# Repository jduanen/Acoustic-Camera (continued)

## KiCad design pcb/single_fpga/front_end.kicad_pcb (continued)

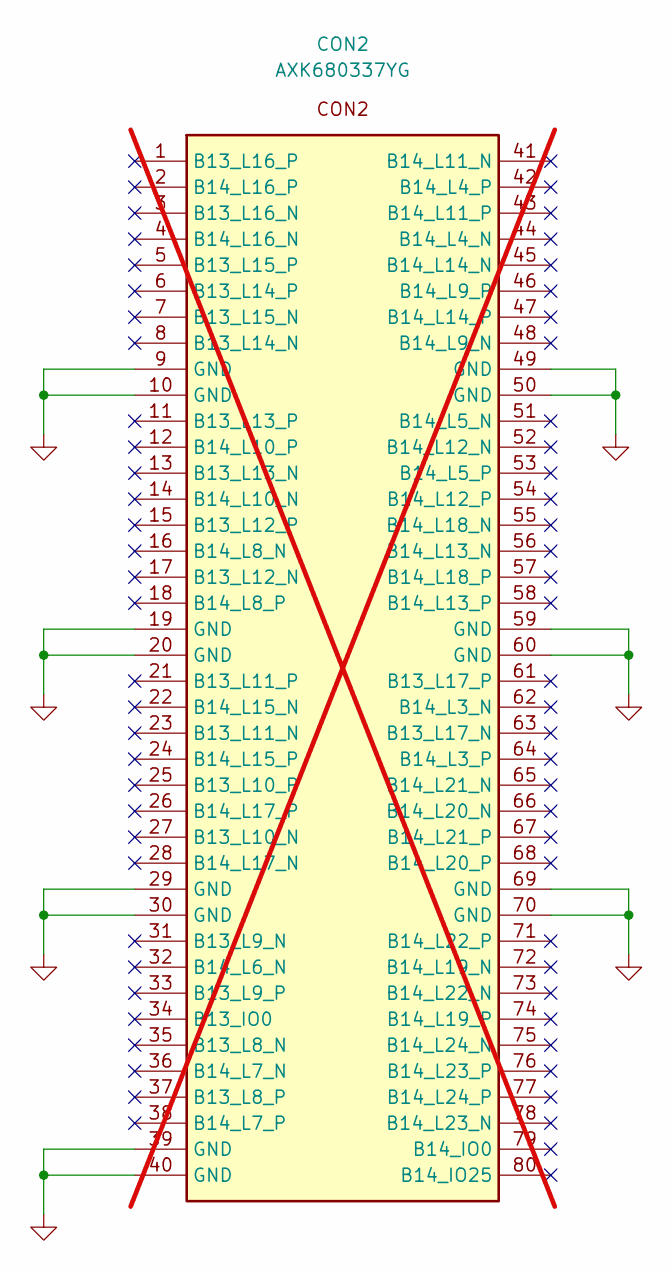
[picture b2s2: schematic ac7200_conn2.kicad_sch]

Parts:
CON2: AXK680337YG; Part Number AXK680337YG; LCSC Part # C2848859; not fitted

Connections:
GND: CON2.9 (GND), CON2.10 (GND), CON2.19 (GND), CON2.20 (GND), CON2.29 (GND), CON2.30 (GND), CON2.39 (GND), CON2.40 (GND), CON2.49 (GND), CON2.50 (GND), CON2.59 (GND), CON2.60 (GND), CON2.69 (GND), CON2.70 (GND); also elsewhere on the board

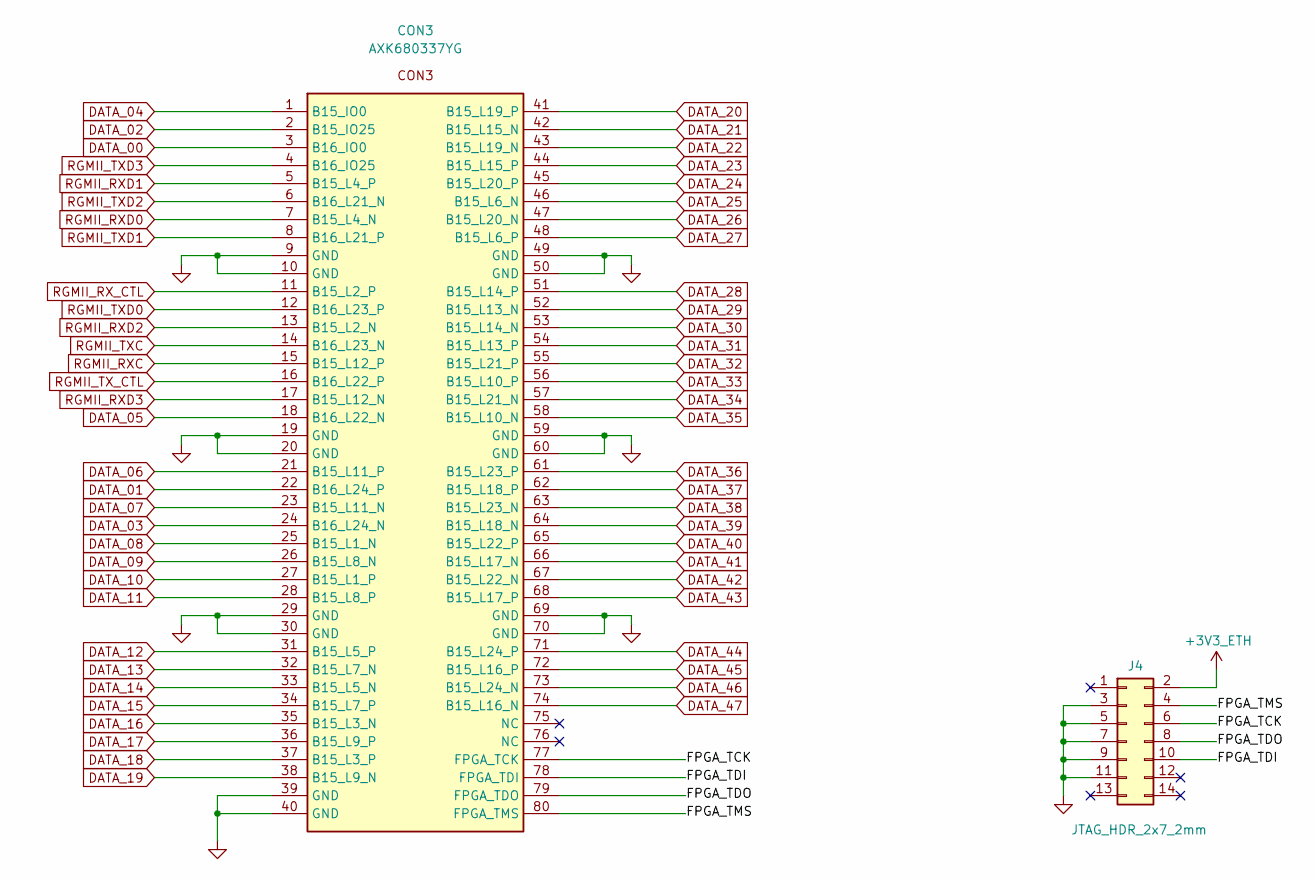
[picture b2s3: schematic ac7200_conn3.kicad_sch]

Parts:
CON3: AXK680337YG; Part Number AXK680337YG; LCSC Part # C2848859
J4: JTAG_HDR_2x7_2mm; PinHeader_2x07_P2.00mm_Vertical; Part Number PZ200-2-07-Z; LCSC Part # C2905993

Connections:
+3V3_ETH: J4.2; also elsewhere on the board
/AC7200 Conn3/FPGA_TCK: CON3.77 (FPGA_TCK), J4.6
/AC7200 Conn3/FPGA_TDI: CON3.78 (FPGA_TDI), J4.10
/AC7200 Conn3/FPGA_TDO: CON3.79 (FPGA_TDO), J4.8
/AC7200 Conn3/FPGA_TMS: CON3.80 (FPGA_TMS), J4.4
DATA_00: CON3.3 (B16_IO0); also elsewhere on the board
DATA_01: CON3.22 (B16_L24_P); also elsewhere on the board
DATA_02: CON3.2 (B15_IO25); also elsewhere on the board
DATA_03: CON3.24 (B16_L24_N); also elsewhere on the board
DATA_04: CON3.1 (B15_IO0); also elsewhere on the board
DATA_05: CON3.18 (B16_L22_N); also elsewhere on the board
DATA_06: CON3.21 (B15_L11_P); also elsewhere on the board
DATA_07: CON3.23 (B15_L11_N); also elsewhere on the board
DATA_08: CON3.25 (B15_L1_N); also elsewhere on the board
DATA_09: CON3.26 (B15_L8_N); also elsewhere on the board
DATA_10: CON3.27 (B15_L1_P); also elsewhere on the board
DATA_11: CON3.28 (B15_L8_P); also elsewhere on the board
DATA_12: CON3.31 (B15_L5_P); also elsewhere on the board
DATA_13: CON3.32 (B15_L7_N); also elsewhere on the board
DATA_14: CON3.33 (B15_L5_N); also elsewhere on the board
DATA_15: CON3.34 (B15_L7_P); also elsewhere on the board
DATA_16: CON3.35 (B15_L3_N); also elsewhere on the board
DATA_17: CON3.36 (B15_L9_P); also elsewhere on the board
DATA_18: CON3.37 (B15_L3_P); also elsewhere on the board
DATA_19: CON3.38 (B15_L9_N); also elsewhere on the board
DATA_20: CON3.41 (B15_L19_P); also elsewhere on the board
DATA_21: CON3.42 (B15_L15_N); also elsewhere on the board
DATA_22: CON3.43 (B15_L19_N); also elsewhere on the board
DATA_23: CON3.44 (B15_L15_P); also elsewhere on the board
DATA_24: CON3.45 (B15_L20_P); also elsewhere on the board
DATA_25: CON3.46 (B15_L6_N); also elsewhere on the board
DATA_26: CON3.47 (B15_L20_N); also elsewhere on the board
DATA_27: CON3.48 (B15_L6_P); also elsewhere on the board
DATA_28: CON3.51 (B15_L14_P); also elsewhere on the board
DATA_29: CON3.52 (B15_L13_N); also elsewhere on the board
DATA_30: CON3.53 (B15_L14_N); also elsewhere on the board
DATA_31: CON3.54 (B15_L13_P); also elsewhere on the board
DATA_32: CON3.55 (B15_L21_P); also elsewhere on the board
DATA_33: CON3.56 (B15_L10_P); also elsewhere on the board
DATA_34: CON3.57 (B15_L21_N); also elsewhere on the board
DATA_35: CON3.58 (B15_L10_N); also elsewhere on the board
DATA_36: CON3.61 (B15_L23_P); also elsewhere on the board
DATA_37: CON3.62 (B15_L18_P); also elsewhere on the board
DATA_38: CON3.63 (B15_L23_N); also elsewhere on the board
DATA_39: CON3.64 (B15_L18_N); also elsewhere on the board
DATA_40: CON3.65 (B15_L22_P); also elsewhere on the board
DATA_41: CON3.66 (B15_L17_N); also elsewhere on the board
DATA_42: CON3.67 (B15_L22_N); also elsewhere on the board
DATA_43: CON3.68 (B15_L17_P); also elsewhere on the board
DATA_44: CON3.71 (B15_L24_P); also elsewhere on the board
DATA_45: CON3.72 (B15_L16_P); also elsewhere on the board
DATA_46: CON3.73 (B15_L24_N); also elsewhere on the board
DATA_47: CON3.74 (B15_L16_N); also elsewhere on the board
GND: CON3.9 (GND), CON3.10 (GND), CON3.19 (GND), CON3.20 (GND), CON3.29 (GND), CON3.30 (GND), CON3.39 (GND), CON3.40 (GND), CON3.49 (GND), CON3.50 (GND), CON3.59 (GND), CON3.60 (GND), CON3.69 (GND), CON3.70 (GND), J4.3, J4.5, J4.7, J4.9, J4.11; also elsewhere on the board
RGMII_RXC: CON3.15 (B15_L12_P); also elsewhere on the board
RGMII_RXD0: CON3.7 (B15_L4_N); also elsewhere on the board
RGMII_RXD1: CON3.5 (B15_L4_P); also elsewhere on the board
RGMII_RXD2: CON3.13 (B15_L2_N); also elsewhere on the board
RGMII_RXD3: CON3.17 (B15_L12_N); also elsewhere on the board
RGMII_RX_CTL: CON3.11 (B15_L2_P); also elsewhere on the board
RGMII_TXC: CON3.14 (B16_L23_N); also elsewhere on the board
RGMII_TXD0: CON3.12 (B16_L23_P); also elsewhere on the board
RGMII_TXD1: CON3.8 (B16_L21_P); also elsewhere on the board
RGMII_TXD2: CON3.6 (B16_L21_N); also elsewhere on the board
RGMII_TXD3: CON3.4 (B16_IO25); also elsewhere on the board
RGMII_TX_CTL: CON3.16 (B16_L22_P); also elsewhere on the board

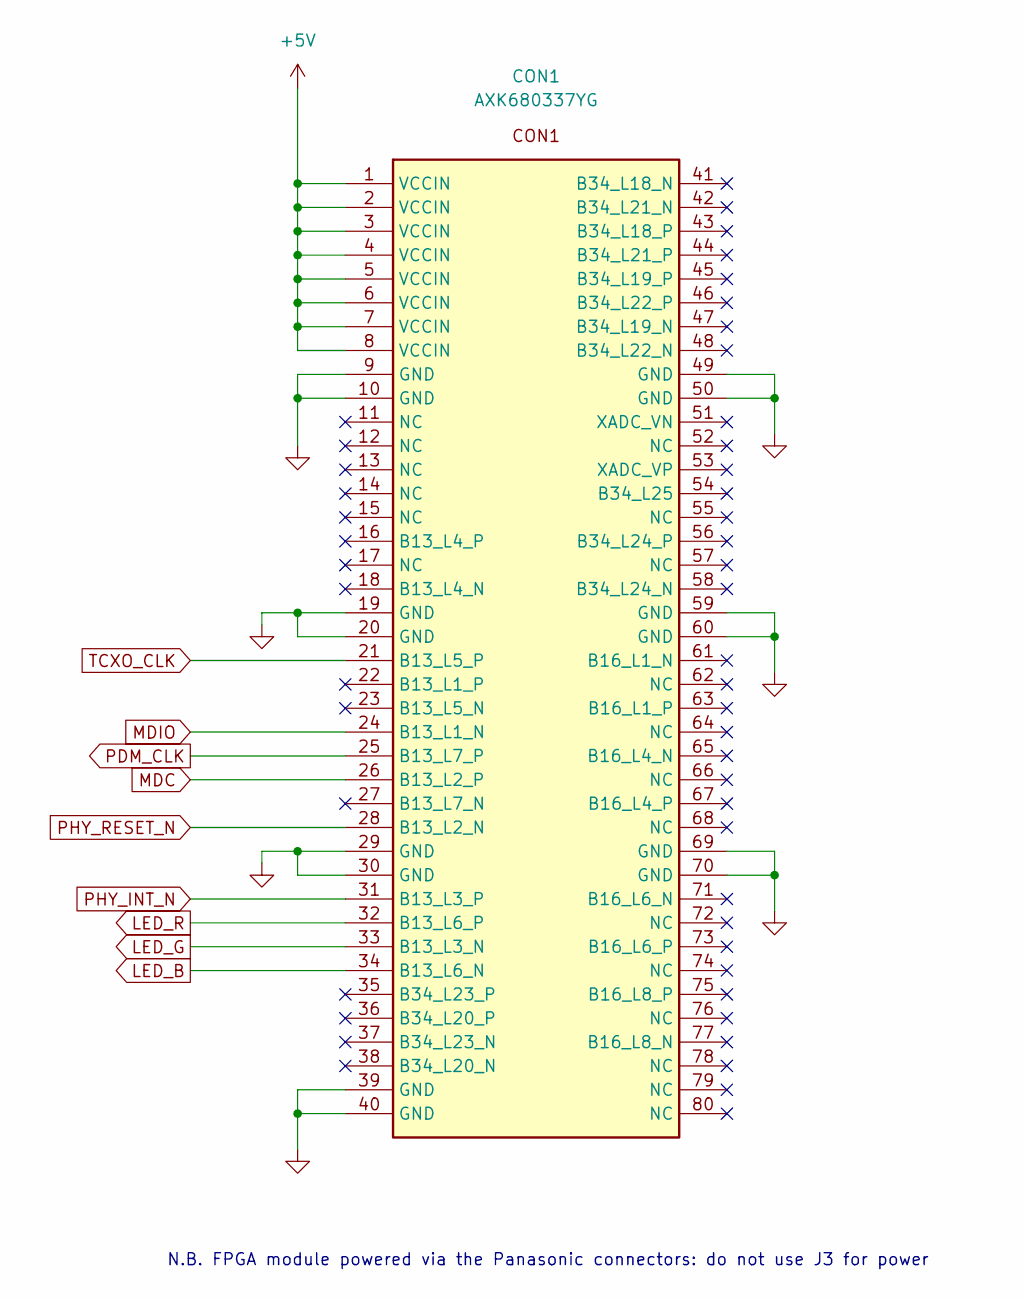
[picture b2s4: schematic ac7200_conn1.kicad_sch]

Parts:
CON1: AXK680337YG; Part Number AXK680337YG; LCSC Part # C2848859

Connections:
+5V: CON1.1 (VCCIN), CON1.2 (VCCIN), CON1.3 (VCCIN), CON1.4 (VCCIN), CON1.5 (VCCIN), CON1.6 (VCCIN), CON1.7 (VCCIN), CON1.8 (VCCIN); also elsewhere on the board
GND: CON1.9 (GND), CON1.10 (GND), CON1.19 (GND), CON1.20 (GND), CON1.29 (GND), CON1.30 (GND), CON1.39 (GND), CON1.40 (GND), CON1.49 (GND), CON1.50 (GND), CON1.59 (GND), CON1.60 (GND), CON1.69 (GND), CON1.70 (GND); also elsewhere on the board
LED_B: CON1.34 (B13_L6_N); also elsewhere on the board
LED_G: CON1.33 (B13_L3_N); also elsewhere on the board
LED_R: CON1.32 (B13_L6_P); also elsewhere on the board
MDC: CON1.26 (B13_L2_P); also elsewhere on the board
MDIO: CON1.24 (B13_L1_N); also elsewhere on the board
PDM_CLK: CON1.25 (B13_L7_P); also elsewhere on the board
PHY_INT_N: CON1.31 (B13_L3_P); also elsewhere on the board
PHY_RESET_N: CON1.28 (B13_L2_N); also elsewhere on the board
TCXO_CLK: CON1.21 (B13_L5_P); also elsewhere on the board

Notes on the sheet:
N.B. FPGA module powered via the Panasonic connectors: do not use J3 for power

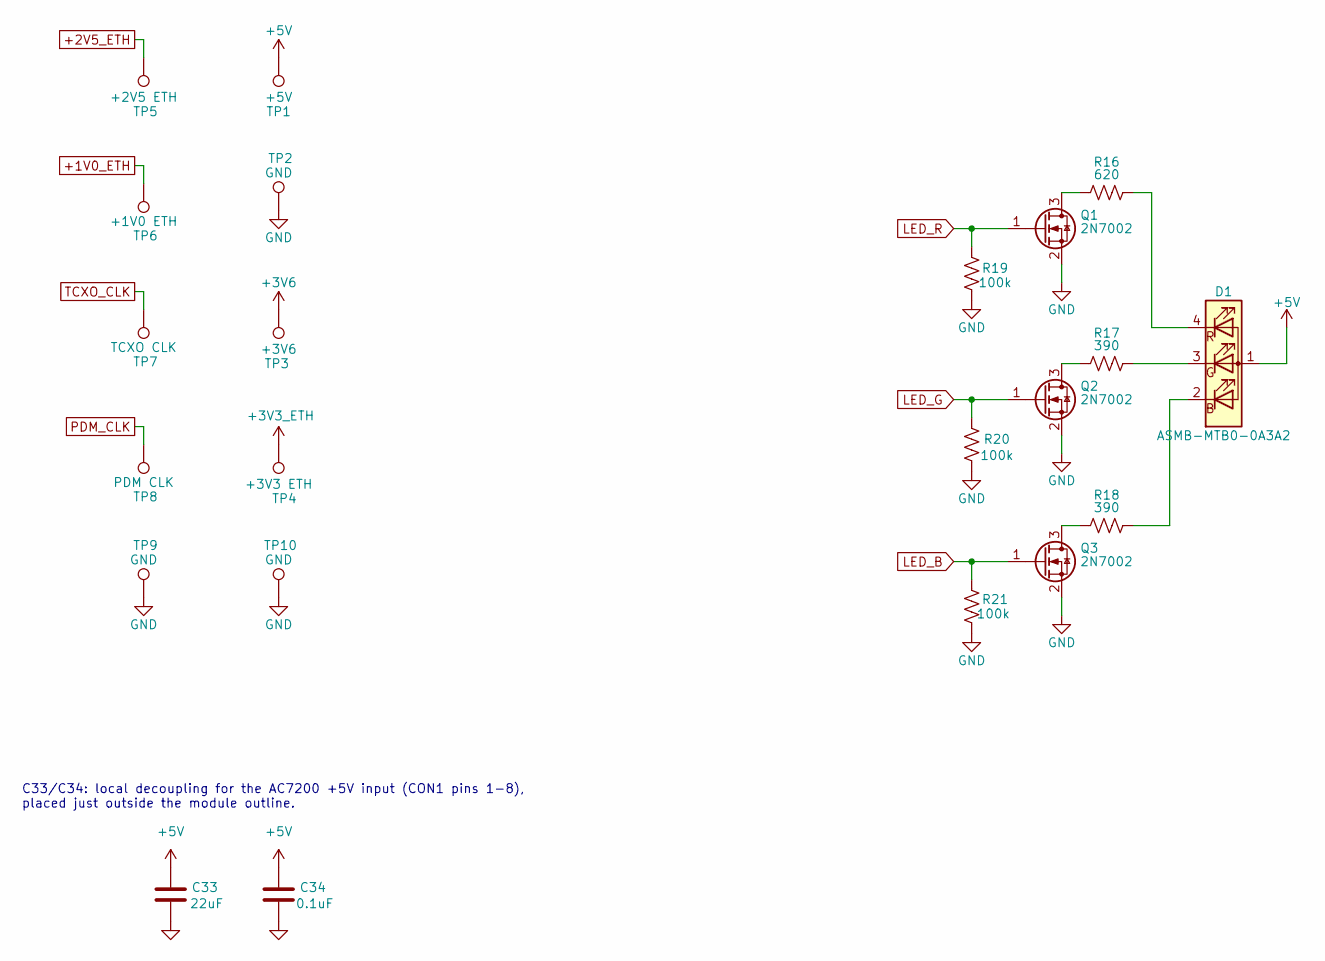
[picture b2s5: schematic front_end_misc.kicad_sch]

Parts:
C33: 22uF; C_0805_2012Metric; Part Number CL21A226MAQNNNE; LCSC Part # C45783
C34: 0.1uF; C_0402_1005Metric; Part Number CL05B104KO5NNNC; LCSC Part # C1525
D1: ASMB-MTB0-0A3A2; LED_Avago_PLCC4_3.2x2.8mm_CW; Part Number ASMB-MTB0-0A3A2; LCSC Part # C2686824
Q1, Q2, Q3: 2N7002; SOT-23; Part Number 2N7002; LCSC Part # C8545
R16: 620; R_0603_1608Metric; Part Number 0603WAF6200T5E; LCSC Part # C23220
R17, R18: 390; R_0603_1608Metric; Part Number 0603WAF3900T5E; LCSC Part # C23151
R19, R20, R21: 100k; R_0603_1608Metric; Part Number 0603WAF1003T5E; LCSC Part # C25803
TP1: +5V; TestPoint_THTPad_D2.0mm_Drill1.0mm
TP2, TP9, TP10: GND; TestPoint_THTPad_D2.0mm_Drill1.0mm
TP3: +3V6; TestPoint_THTPad_D2.0mm_Drill1.0mm
TP4: +3V3 ETH; TestPoint_THTPad_D2.0mm_Drill1.0mm
TP5: +2V5 ETH; TestPoint_THTPad_D2.0mm_Drill1.0mm
TP6: +1V0 ETH; TestPoint_THTPad_D2.0mm_Drill1.0mm
TP7: TCXO CLK; TestPoint_THTPad_D2.0mm_Drill1.0mm
TP8: PDM CLK; TestPoint_THTPad_D2.0mm_Drill1.0mm

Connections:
+1V0_ETH: TP6.1 (1_1); also elsewhere on the board
+2V5_ETH: TP5.1 (1_1); also elsewhere on the board
+3V3_ETH: TP4.1 (1_1); also elsewhere on the board
+3V6: TP3.1 (1_1); also elsewhere on the board
+5V: C33.1, C34.1, D1.1 (A), TP1.1 (1_1); also elsewhere on the board
GND: C33.2, C34.2, Q1.2 (S), Q2.2 (S), Q3.2 (S), R19.1, R20.1, R21.1, TP2.1 (1_1), TP9.1 (1_1), TP10.1 (1_1); also elsewhere on the board
LED_B: Q3.1 (G), R21.2; also elsewhere on the board
LED_G: Q2.1 (G), R20.2; also elsewhere on the board
LED_R: Q1.1 (G), R19.2; also elsewhere on the board
unnamed: D1.2 (BK), R18.1
unnamed: D1.3 (GK), R17.1
unnamed: D1.4 (RK), R16.1
unnamed: Q1.3 (D), R16.2
unnamed: Q2.3 (D), R17.2
unnamed: Q3.3 (D), R18.2
PDM_CLK: TP8.1 (1_1); also elsewhere on the board
TCXO_CLK: TP7.1 (1_1); also elsewhere on the board

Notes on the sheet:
C33/C34: local decoupling for the AC7200 +5V input (CON1 pins 1-8), placed just outside the module outline.

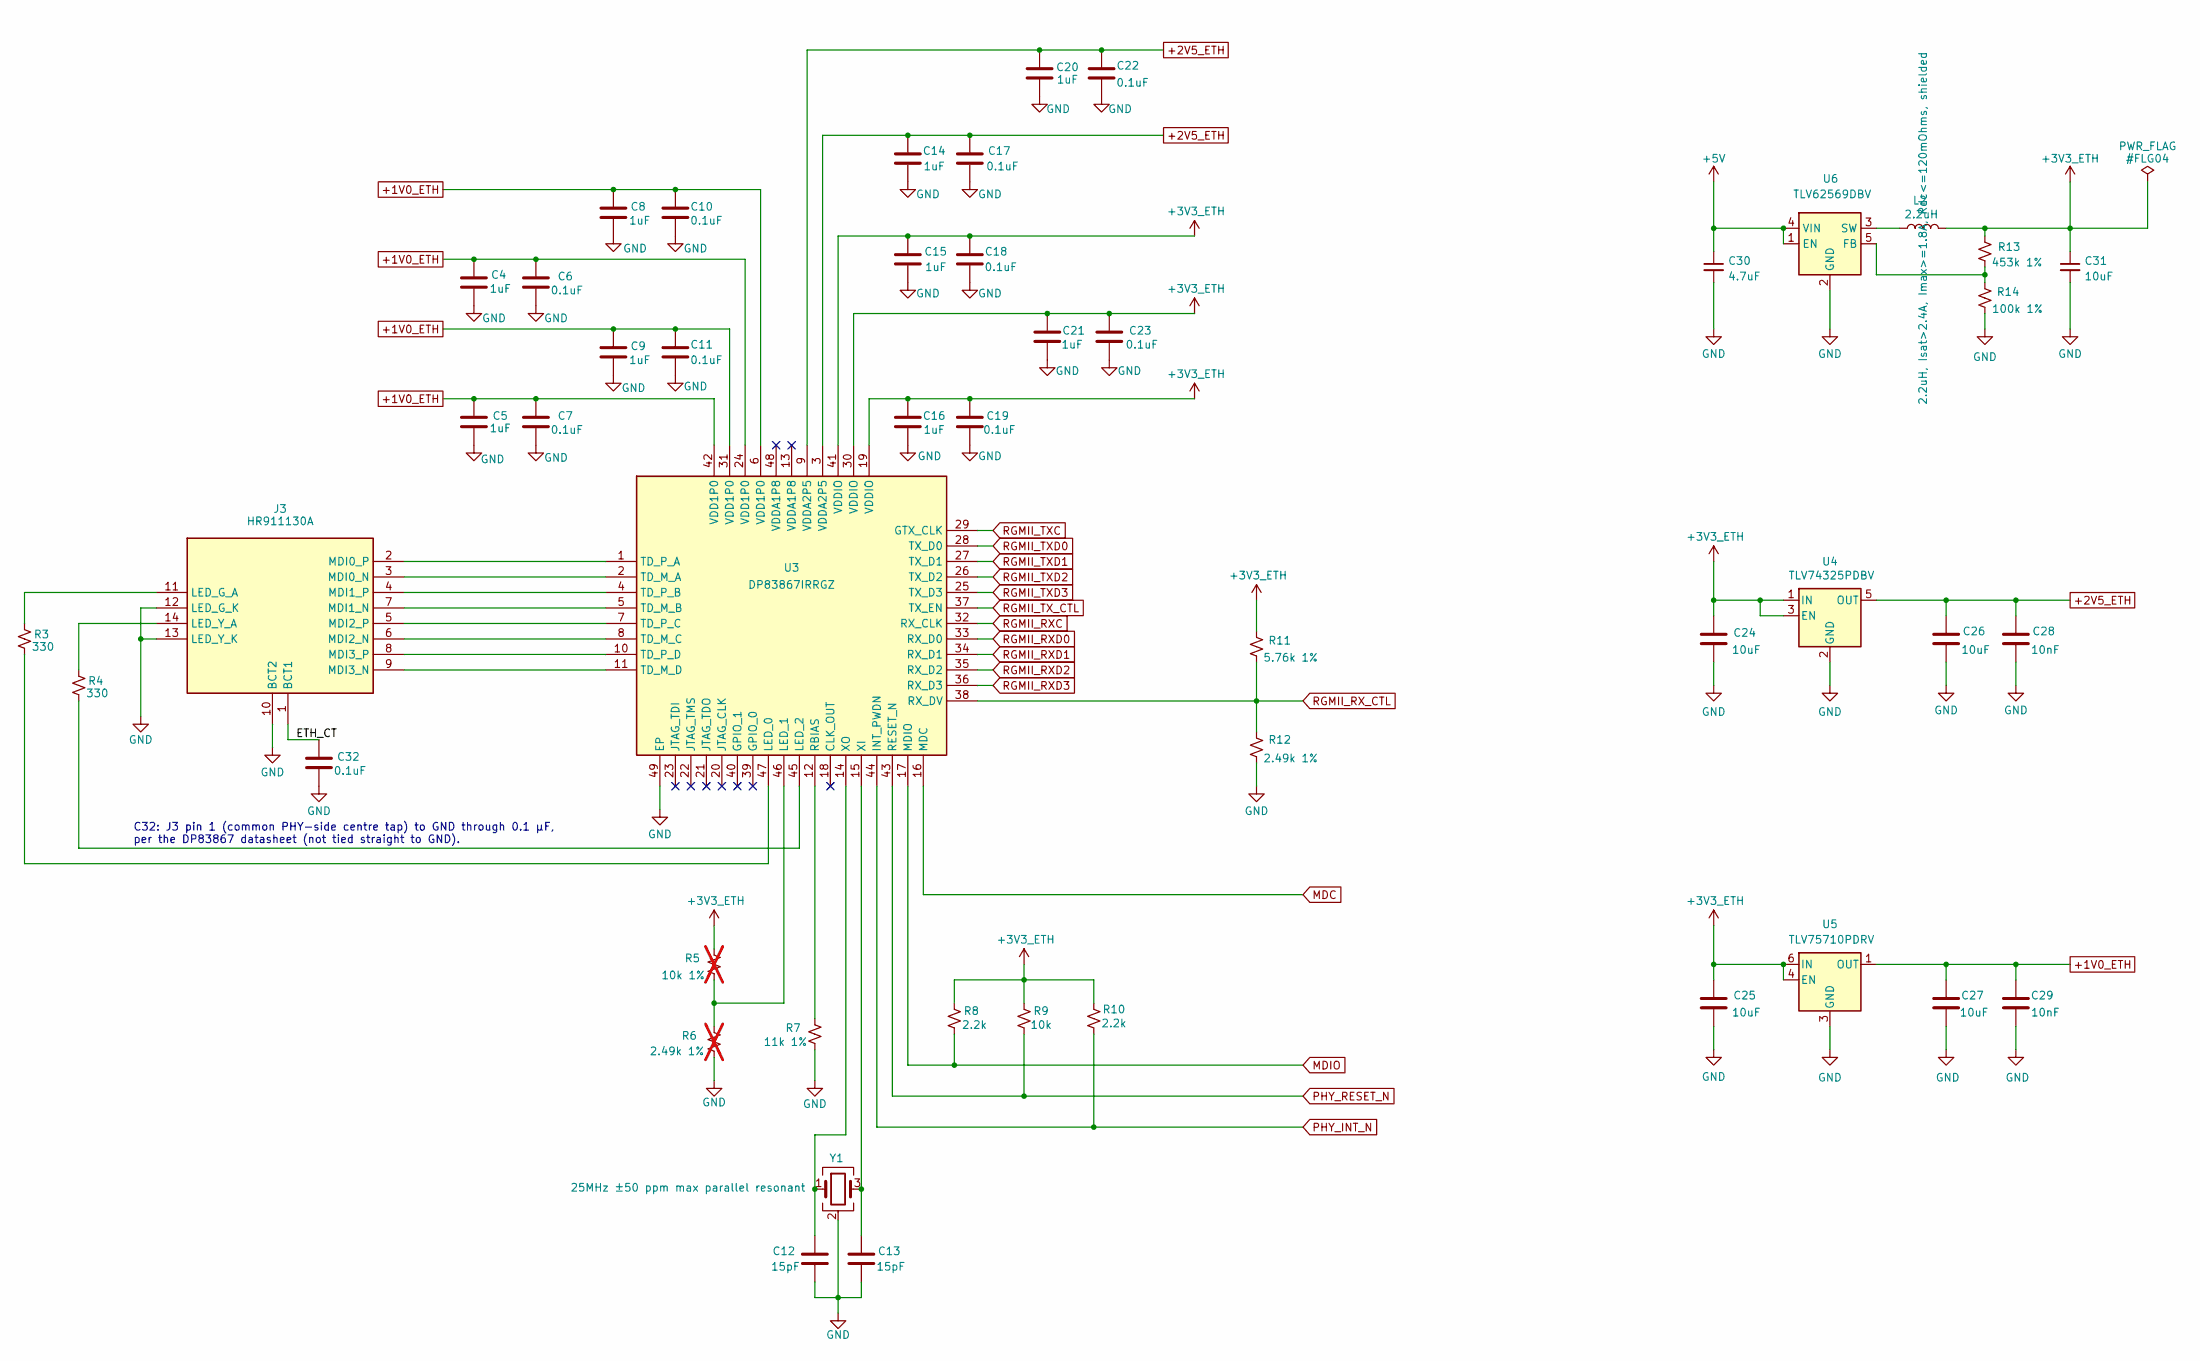
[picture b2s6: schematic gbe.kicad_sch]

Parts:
C4, C5, C8, C9, C14, C15, C16, C20, C21: 1uF; C_0402_1005Metric; Part Number CL05A105KA5NQNC; LCSC Part # C52923
C6, C7, C10, C11, C17, C18, C19, C22, C23, C32: 0.1uF; C_0402_1005Metric; Part Number CL05B104KO5NNNC; LCSC Part # C1525
C12, C13: 15pF; C_0402_1005Metric; Part Number 0402CG150J500NT; LCSC Part # C1548
C24, C25, C26, C27: 10uF; C_0603_1608Metric; Part Number CL10A106KP8NNNC; LCSC Part # C19702
C28, C29: 10nF; C_0603_1608Metric; Part Number 0603B103K500NT; LCSC Part # C57112
C30: 4.7uF; C_0805_2012Metric; Voltage 16V; Tolerance 10%; Part Number CL21B475KOFNNNE; LCSC Part # C107365
C31: 10uF; C_0805_2012Metric; Voltage 10V; Tolerance 10%; Part Number GRM21BR71A106KE51L; LCSC Part # C86038
J3: HR911130A; Part Number HR911130A; LCSC Part # C54408
L2: 2.2uH; L_Murata_DFE201610P; Part Number DFE201612E-2R2M=P2; LCSC Part # C337893
R3, R4: 330; R_0402_1005Metric; Part Number 0402WGF3300TCE; LCSC Part # C25104
R5: 10k 1%; R_0402_1005Metric; not fitted
R6: 2.49k 1%; R_0402_1005Metric; Part Number 0402WGF2491TCE; LCSC Part # C25884; not fitted
R7: 11k 1%; R_0402_1005Metric; Part Number 0402WGF1102TCE; LCSC Part # C25749
R8, R10: 2.2k; R_0402_1005Metric; Part Number 0402WGF2201TCE; LCSC Part # C25879
R9: 10k; R_0402_1005Metric; Part Number 0402WGF1002TCE; LCSC Part # C25744
R11: 5.76k 1%; R_0402_1005Metric; Part Number 0402WGF5761TCE; LCSC Part # C25910
R12: 2.49k 1%; R_0402_1005Metric; Part Number 0402WGF2491TCE; LCSC Part # C25884
R13: 453k 1%; R_0603_1608Metric; Tolerance 1%; Part Number ERJ-3EKF4533V; LCSC Part # C403234
R14: 100k 1%; R_0603_1608Metric; Tolerance 1%; Part Number 0603WAF1003T5E; LCSC Part # C25803
U3: DP83867IRRGZ; VQFN-48-1EP_7x7mm_P0.5mm_EP4.1x4.1mm; Part Number DP83867IRRGZR; LCSC Part # C2678038
U4: TLV74325PDBV; SOT-23-5; Part Number TLV74325PDBVR; LCSC Part # C485154
U5: TLV75710PDRV; WSON-6-1EP_2x2mm_P0.65mm_EP1x1.6mm; Part Number TLV75710PDRVR; LCSC Part # C2861391
U6: TLV62569DBV; SOT-23-5; Part Number TLV62569DBVR; LCSC Part # C141836
Y1: 25MHz ±50 ppm max parallel resonant; Crystal_SMD_3225-4Pin_3.2x2.5mm; Part Number X322525MOB4SI; LCSC Part # C9006

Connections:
+1V0_ETH: C4.1, C5.1, C6.1, C7.1, C8.1, C9.1, C10.1, C11.1, C27.2, C29.2, U3.6 (VDD1P0), U3.24 (VDD1P0), U3.31 (VDD1P0), U3.42 (VDD1P0), U5.1 (OUT); also elsewhere on the board
+2V5_ETH: C14.1, C17.1, C20.1, C22.1, C26.2, C28.2, U3.3 (VDDA2P5), U3.9 (VDDA2P5), U4.5 (OUT); also elsewhere on the board
+3V3_ETH: C15.1, C16.1, C18.1, C19.2, C21.1, C23.1, C24.2, C25.2, C31.1, L2.2, R5.2, R8.1, R9.1, R10.1, R11.2, R13.1, U3.19 (VDDIO), U3.30 (VDDIO), U3.41 (VDDIO), U4.1 (IN), U4.3 (EN), U5.4 (EN), U5.6 (IN); also elsewhere on the board
+5V: C30.1, U6.1 (EN), U6.4 (VIN); also elsewhere on the board
/Ethernet Interface/ETH_CT: C32.1, J3.1 (BCT1)
GND: C4.2, C5.2, C6.2, C7.2, C8.2, C9.2, C10.2, C11.2, C12.2, C13.2, C14.2, C15.2, C16.2, C17.2, C18.2, C19.1, C20.2, C21.2, C22.2, C23.2, C24.1, C25.1, C26.1, C27.1, C28.1, C29.1, C30.2, C31.2, C32.2, J3.10 (BCT2), J3.12 (LED_G_K), J3.13 (LED_Y_K), R6.1, R7.1, R12.1, R14.1, U3.49 (EP), U4.2 (GND), U5.3 (GND), U5.7 (GND), U6.2 (GND), Y1.2 (G), Y1.4 (G); also elsewhere on the board
MDC: U3.16 (MDC); also elsewhere on the board
MDIO: R8.2, U3.17 (MDIO); also elsewhere on the board
unnamed: J3.11 (LED_G_A), R3.1
unnamed: J3.14 (LED_Y_A), R4.2
unnamed: J3.3 (MDI0_N), U3.2 (TD_M_A)
unnamed: J3.2 (MDI0_P), U3.1 (TD_P_A)
unnamed: J3.7 (MDI1_N), U3.5 (TD_M_B)
unnamed: J3.4 (MDI1_P), U3.4 (TD_P_B)
unnamed: J3.6 (MDI2_N), U3.8 (TD_M_C)
unnamed: J3.5 (MDI2_P), U3.7 (TD_P_C)
unnamed: J3.9 (MDI3_N), U3.11 (TD_M_D)
unnamed: J3.8 (MDI3_P), U3.10 (TD_P_D)
unnamed: R3.2, U3.47 (LED_0)
unnamed: R5.1, R6.2, U3.46 (LED_1)
unnamed: R4.1, U3.45 (LED_2)
unnamed: R7.2, U3.12 (RBIAS)
unnamed: C13.1, U3.15 (XI), Y1.3
unnamed: C12.1, U3.14 (XO), Y1.1
unnamed: R13.2, R14.2, U6.5 (FB)
unnamed: L2.1, U6.3 (SW)
PHY_INT_N: R10.2, U3.44 (INT_PWDN); also elsewhere on the board
PHY_RESET_N: R9.2, U3.43 (RESET_N); also elsewhere on the board
RGMII_RXC: U3.32 (RX_CLK); also elsewhere on the board
RGMII_RXD0: U3.33 (RX_D0); also elsewhere on the board
RGMII_RXD1: U3.34 (RX_D1); also elsewhere on the board
RGMII_RXD2: U3.35 (RX_D2); also elsewhere on the board
RGMII_RXD3: U3.36 (RX_D3); also elsewhere on the board
RGMII_RX_CTL: R11.1, R12.2, U3.38 (RX_DV); also elsewhere on the board
RGMII_TXC: U3.29 (GTX_CLK); also elsewhere on the board
RGMII_TXD0: U3.28 (TX_D0); also elsewhere on the board
RGMII_TXD1: U3.27 (TX_D1); also elsewhere on the board
RGMII_TXD2: U3.26 (TX_D2); also elsewhere on the board
RGMII_TXD3: U3.25 (TX_D3); also elsewhere on the board
RGMII_TX_CTL: U3.37 (TX_EN); also elsewhere on the board

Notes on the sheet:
C32: J3 pin 1 (common PHY-side centre tap) to GND through 0.1 µF, per the DP83867 datasheet (not tied straight to GND).

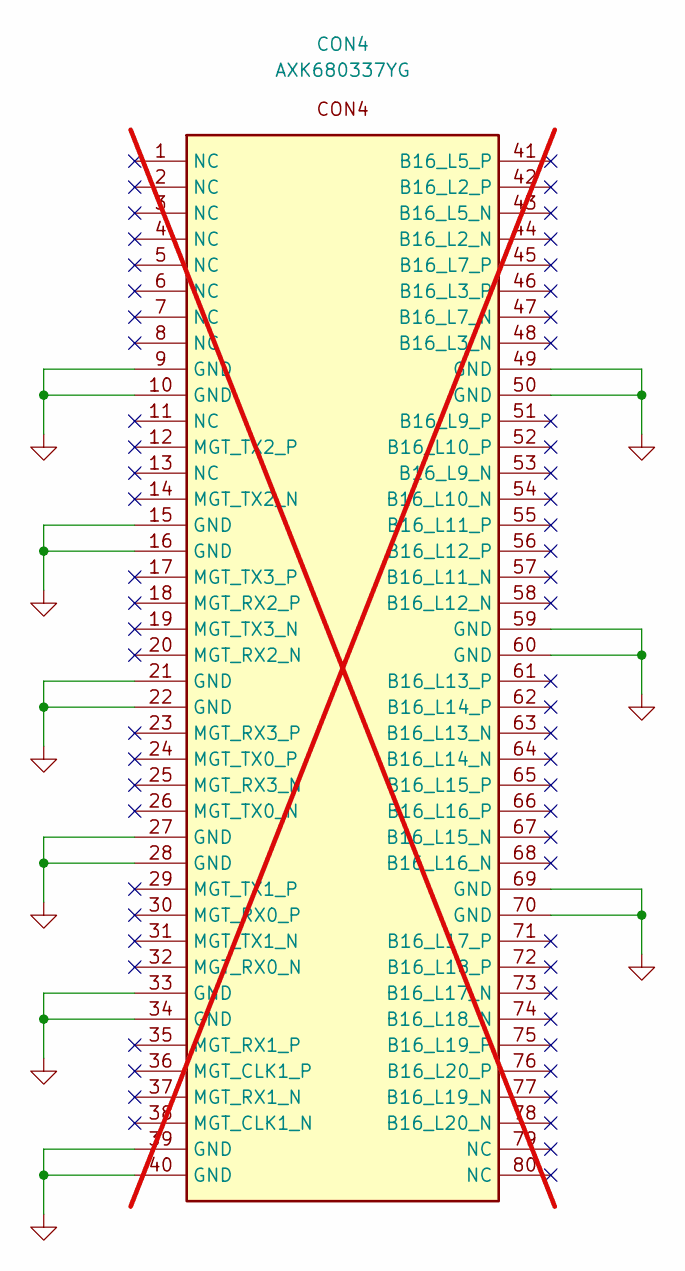
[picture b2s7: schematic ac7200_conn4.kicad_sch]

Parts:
CON4: AXK680337YG; Part Number AXK680337YG; LCSC Part # C2848859; not fitted

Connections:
GND: CON4.9 (GND), CON4.10 (GND), CON4.15 (GND), CON4.16 (GND), CON4.21 (GND), CON4.22 (GND), CON4.27 (GND), CON4.28 (GND), CON4.33 (GND), CON4.34 (GND), CON4.39 (GND), CON4.40 (GND), CON4.49 (GND), CON4.50 (GND), CON4.59 (GND), CON4.60 (GND), CON4.69 (GND), CON4.70 (GND); also elsewhere on the board

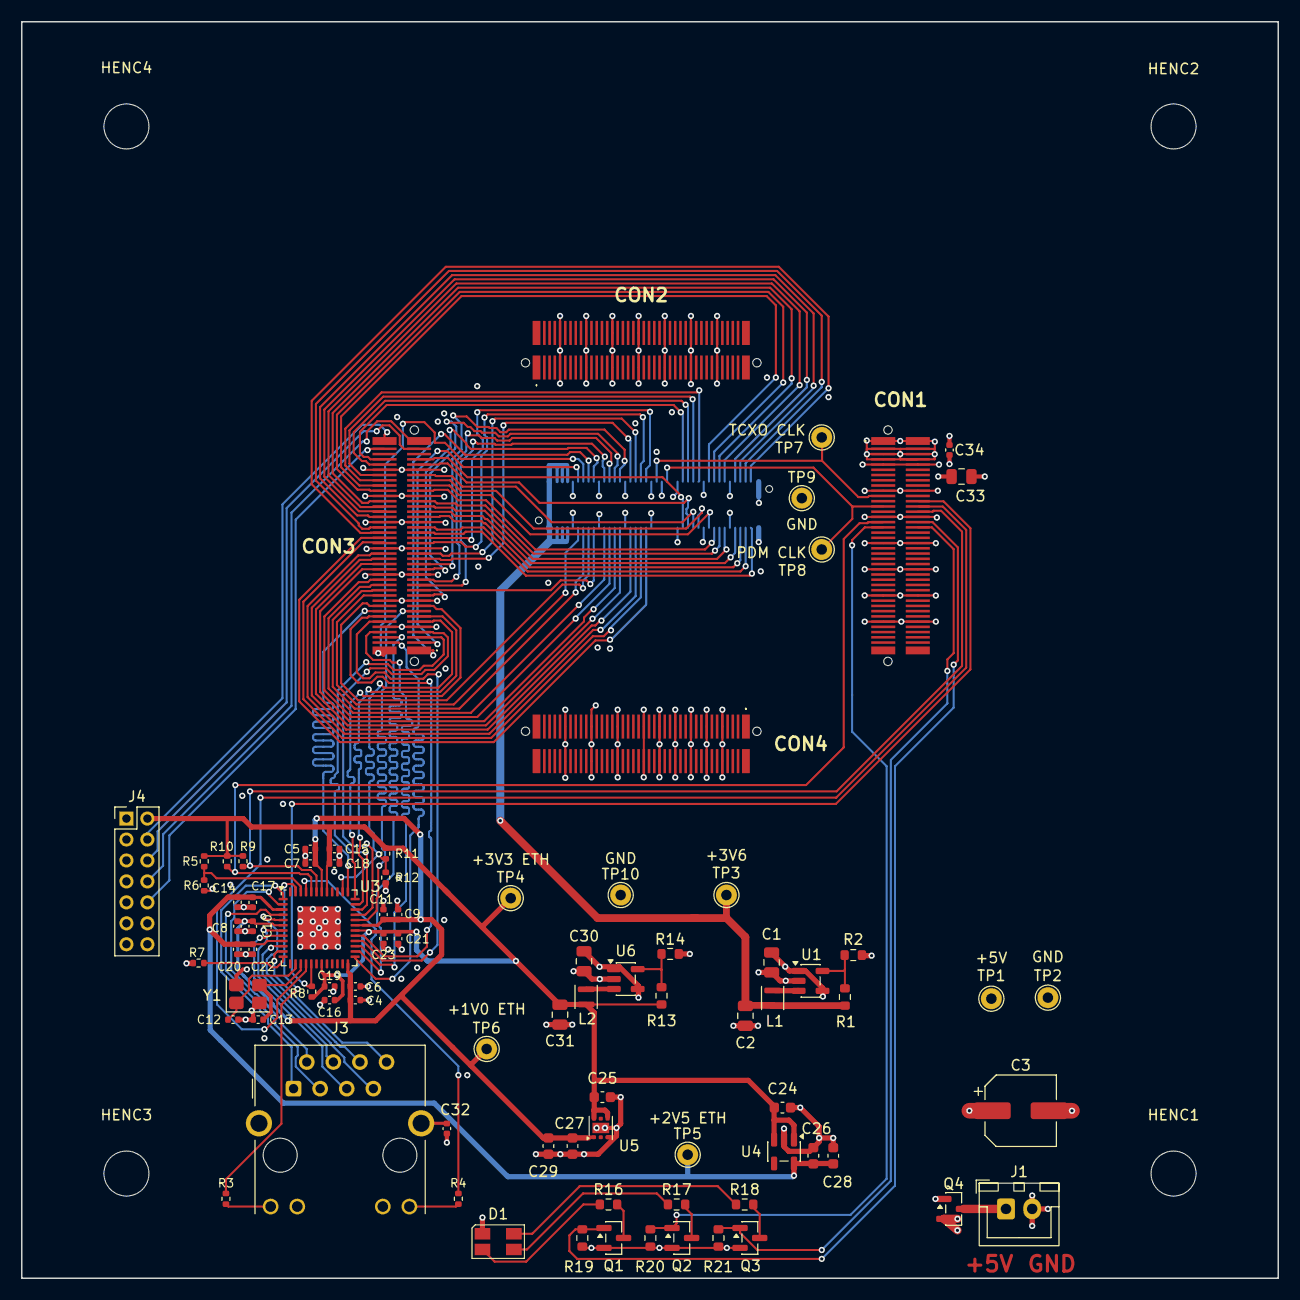
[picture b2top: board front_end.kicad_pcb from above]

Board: 4 copper layers, 120.0 x 120.0 mm, 89 parts (1 on the bottom side), 107 nets.

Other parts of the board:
HENC1, HENC2, HENC3, HENC4: MountingHole_4.3mm_M4

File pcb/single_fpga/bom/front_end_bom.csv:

"Refs","Qty","Value","Footprint","Manufacturer","Part Number","LCSC Part #","PROD_ID","Tolerance","Voltage","Description"
"C1,C30","2","4.7uF","Capacitor_SMD:C_0805_2012Metric","Samsung Electro-Mechanics","CL21B475KOFNNNE","C107365","","10%","16V","Unpolarized capacitor"
"C2,C31","2","10uF","Capacitor_SMD:C_0805_2012Metric","Murata","GRM21BR71A106KE51L","C86038","","10%","10V","Unpolarized capacitor"
"C3","1","100uF","Capacitor_SMD:CP_Elec_6.3x5.8","FOSAN","FVM025ADA101M0654","C7469933","CAP-12547","20%","25V","Polarized capacitor, US symbol, 0.248"" Dia x 0.303"" H, Electrolitic"
"C4,C5,C8,C9,C14,C15,C16,C20,C21","9","1uF","Capacitor_SMD:C_0402_1005Metric","Samsung Electro-Mechanics","CL05A105KA5NQNC","C52923","","","",""
"C6,C7,C10,C11,C17,C18,C19,C22,C23,C32,C34","11","0.1uF","Capacitor_SMD:C_0402_1005Metric","Samsung Electro-Mechanics","CL05B104KO5NNNC","C1525","","","",""
"C12,C13","2","15pF","Capacitor_SMD:C_0402_1005Metric","FH (Guangdong Fenghua)","0402CG150J500NT","C1548","","","",""
"C24,C25,C26,C27","4","10uF","Capacitor_SMD:C_0603_1608Metric","Samsung Electro-Mechanics","CL10A106KP8NNNC","C19702","","","",""
"C28,C29","2","10nF","Capacitor_SMD:C_0603_1608Metric","FH (Guangdong Fenghua)","0603B103K500NT","C57112","","","",""
"C33","1","22uF","Capacitor_SMD:C_0805_2012Metric","Samsung Electro-Mechanics","CL21A226MAQNNNE","C45783","","","",""
"CON1,CON3","2","AXK680337YG","AXK680337YG:AXK680337YG","Panasonic","AXK680337YG","C2848859","","","","Carrier-side CON1 for the ALINX AC7200 SOM: Panasonic AXK680337YG P5K 80-pin 0.5mm header (3.0mm mated, bosses), mating the module's AXK580137YG socket CON1. Pin names are the AC7200 signals on module CON1 (from unit A of 'AC7200 Interface', same pin positions); pin numbers 1-80 are the header's, socket pin n mates header pin n.,Carrier-side CON3 for the ALINX AC7200 SOM: Panasonic AXK680337YG P5K 80-pin 0.5mm header (3.0mm mated, bosses), mating the module's AXK580137YG socket CON3. Pin names are the AC7200 signals on module CON3 (from unit C of 'AC7200 Interface', same pin positions); pin numbers 1-80 are the header's, socket pin n mates header pin n."
"D1","1","ASMB-MTB0-0A3A2","LED_SMD:LED_Avago_PLCC4_3.2x2.8mm_CW","Broadcom","ASMB-MTB0-0A3A2","C2686824","","","","Tricolor Black Surface LED, Common Anode Pin 1, PLCC-4"
"J1","1","Main Power Input","Connector_JST:JST_XH_B2B-XH-A_1x02_P2.50mm_Vertical","JST","B2B-XH-A(LF)(SN)","C158012","","","","Generic connector, single row, 01x02, script generated (kicad-library-utils/schlib/autogen/connector/)"
"J2","1","AXK5S80337YG","AXK5S80337YG:AXK5S80337YG","Panasonic","AXK5S80337YG","","","","","Panasonic AXK5S80337YG -- P5KS 0.5mm-pitch 80-pin board-to-board SOCKET, 7.0/8.0/9.0mm mated height, with positioning bosses. Mates AXK6S80637YG at 9.0mm."
"J3","1","HR911130A","HR911130A:HR911130A","HanRun","HR911130A","C54408","","","","Single-port 10/100/1000Base-T RJ45 jack with integrated magnetics + Bob-Smith termination + Green/Yellow LEDs"
"J4","1","JTAG_HDR_2x7_2mm","Connector_PinHeader_2.00mm:PinHeader_2x07_P2.00mm_Vertical","HCTL","PZ200-2-07-Z","C2905993","","","","Xilinx Platform Cable USB JTAG target header (DS593 pinout)"
"L1,L2","2","2.2uH","Inductor_SMD:L_Murata_DFE201610P","Murata","DFE201612E-2R2M=P2","C337893","","","","2.2uH, Isat>2.4A, Imax>=1.8A, Rdc<=120mOhms, shielded"
"Q1,Q2,Q3","3","2N7002","Package_TO_SOT_SMD:SOT-23","JSCJ","2N7002","C8545","","","","0.115A Id, 60V Vds, N-Channel MOSFET, SOT-23"
"Q4","1","AO3401A","Package_TO_SOT_SMD:SOT-23","AOS","AO3401A","C15127","","","","Reverse-polarity protection for the +5V input (gate to GND: conducts only with correct polarity)"
"R1","1","499k","Resistor_SMD:R_0603_1608Metric","YAGEO","RC0603FR-07499KL","C131054","","1%","","Resistor"
"R2","1","100k","Resistor_SMD:R_0603_1608Metric","UNI-ROYAL","0603WAF1003T5E","C25803","","1%","","Resistor"
"R3,R4","2","330","PCM_SparkFun-Resistor:R_0402_1005Metric","UNI-ROYAL","0402WGF3300TCE","C25104","RES-15407","","","Resistor"
"R7","1","11k 1%","PCM_SparkFun-Resistor:R_0402_1005Metric","UNI-ROYAL","0402WGF1102TCE","C25749","RES-25567","","","Resistor"
"R8,R10","2","2.2k","SparkFun-Resistor:R_0402_1005Metric","UNI-ROYAL","0402WGF2201TCE","C25879","RES-08272","","","Resistor"
"R9","1","10k","SparkFun-Resistor:R_0402_1005Metric","UNI-ROYAL","0402WGF1002TCE","C25744","RES-00824","","","Resistor"
"R11","1","5.76k 1%","PCM_SparkFun-Resistor:R_0402_1005Metric","UNI-ROYAL","0402WGF5761TCE","C25910","RES-25566","","","Resistor"
"R12","1","2.49k 1%","PCM_SparkFun-Resistor:R_0402_1005Metric","UNI-ROYAL","0402WGF2491TCE","C25884","RES-25566","","","Resistor"
"R13","1","453k 1%","Resistor_SMD:R_0603_1608Metric","Panasonic","ERJ-3EKF4533V","C403234","","1%","","Resistor"
"R14","1","100k 1%","Resistor_SMD:R_0603_1608Metric","UNI-ROYAL","0603WAF1003T5E","C25803","","1%","","Resistor"
"R16","1","620","PCM_SparkFun-Resistor:R_0603_1608Metric","UNI-ROYAL","0603WAF6200T5E","C23220","RES-07856","","","Resistor"
"R17,R18","2","390","PCM_SparkFun-Resistor:R_0603_1608Metric","UNI-ROYAL","0603WAF3900T5E","C23151","RES-07856","","","Resistor"
"R19,R20,R21","3","100k","PCM_SparkFun-Resistor:R_0603_1608Metric","UNI-ROYAL","0603WAF1003T5E","C25803","RES-07856","","","Resistor"
"U1,U6","2","TLV62569DBV","Package_TO_SOT_SMD:SOT-23-5","Texas Instruments","TLV62569DBVR","C141836","","","","High Efficiency Synchronous Buck Converter, Adjustable Output 0.6V-5.5V, 2A, SOT-23-5"
"U3","1","DP83867IRRGZ","Package_DFN_QFN:VQFN-48-1EP_7x7mm_P0.5mm_EP4.1x4.1mm","Texas Instruments","DP83867IRRGZR","C2678038","","","",""
"U4","1","TLV74325PDBV","Package_TO_SOT_SMD:SOT-23-5","Texas Instruments","TLV74325PDBVR","C485154","","","","500mA Low Dropout Voltage Regulator, Fixed Output 2.5V, SOT-23-5"
"U5","1","TLV75710PDRV","Package_SON:WSON-6-1EP_2x2mm_P0.65mm_EP1x1.6mm","Texas Instruments","TLV75710PDRVR","C2861391","","","","500mA Low Dropout Voltage Regulator, Fixed Output 1.0V, WSON6"
"Y1","1","25MHz ±50 ppm max parallel resonant","Crystal:Crystal_SMD_3225-4Pin_3.2x2.5mm","YXC","X322525MOB4SI","C9006","","","","Four pin crystal, GND on pins 2 and 4"
